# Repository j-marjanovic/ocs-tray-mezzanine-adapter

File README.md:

# OCS Tray Mezzanine Adapter, version 1

## The adapter in action

Here we can see the adapter board connecting the PCIe (x1, over USB) to the FPGA
board, 12V power from the ATX power supply, and I2C to the Raspberry Pi.

## revA

[Schematics as PDF](production/revA/ocp-tray-mezzanine-adapter-v1-revA.pdf)

Known limitations/errors:

  * Samtec connector is rotated by 180 deg - the keying pins on the sides need
    to be trimmed
  * Pin 4 on the USB should be not be connected to the board; it should either
    be trimmed before soldering or the via should be removed
  * The mounting hole is slightly misaligned

## TODO for revB

  * solder mask keep-out for PCIe lanes 7, 8 and 15
  * solder mask keep-out for layer indicators
  * move label R2 (silkscreen over pad)
  * (optional) labels for SDA, SCL and GND on MEZZ I2C connector
  * mode capacitors C1 and C5 to the other side (shorter traces)
  * pin 1 and 4 on the USB connector carry the PCIe signals, fix the connections
  * the LED for the mezzanine present signals has wrong polarity, it should be
    powered from 3V3
  * fix the orientation of the Samtec connector
  * fix the alignment of the mounting hole

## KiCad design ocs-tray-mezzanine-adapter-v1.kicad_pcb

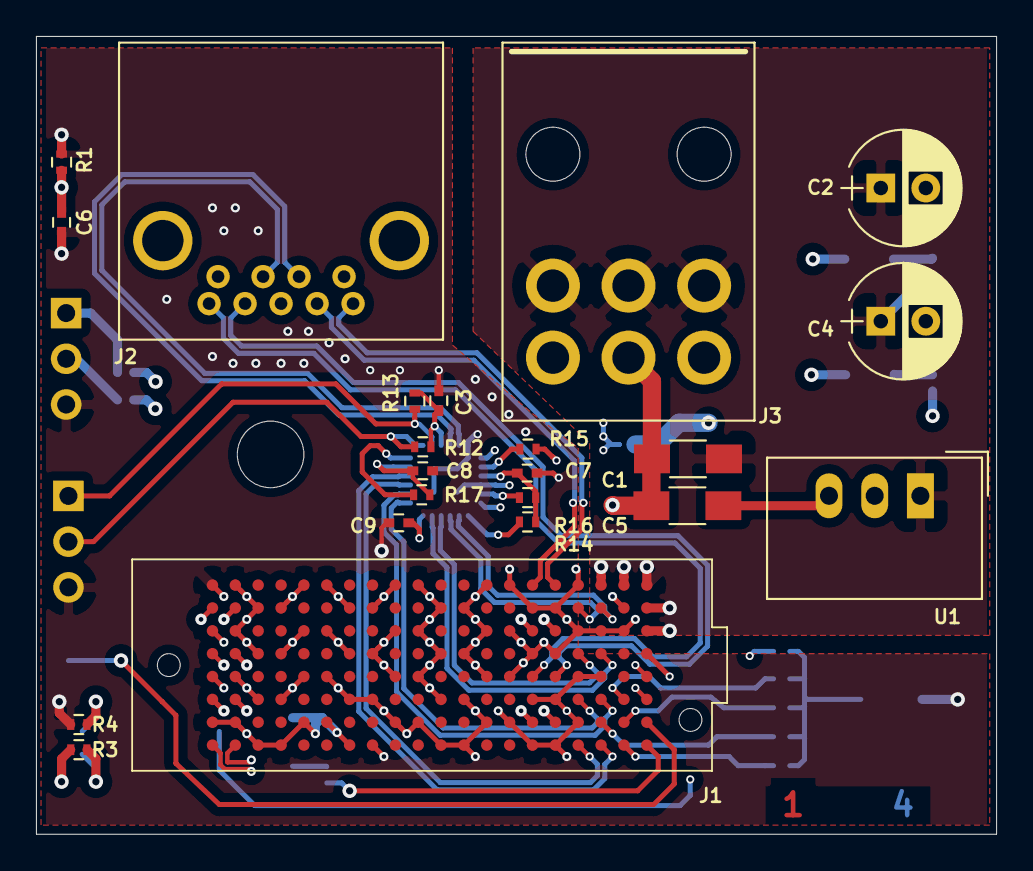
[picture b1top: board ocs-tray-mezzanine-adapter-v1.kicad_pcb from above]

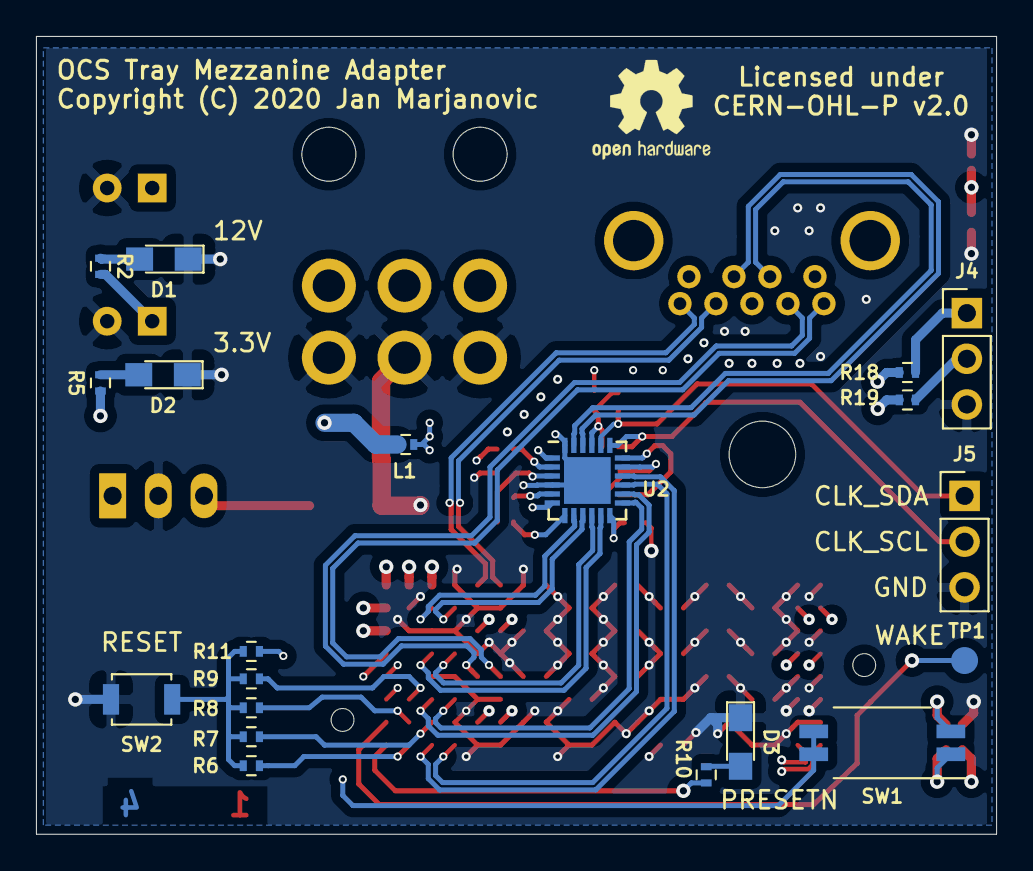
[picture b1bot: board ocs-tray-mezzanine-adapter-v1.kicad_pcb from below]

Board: 4 copper layers, 53.3 x 44.3 mm, 43 parts (20 on the bottom side), 40 nets.

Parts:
C1, C5: 10u; C_1206_HandSoldering
C2, C4: 100uA; CP_Radial_D6.3mm_P2.50mm
C3, C6, C7, C8, C9: 100n; C_0402
D1, D2, D3: LED; LED_0805_HandSoldering
H1: MountingHole; MountingHole_3.7mm
J1: SEAF-20-06.5-L-08-2-A-K-TR; samtec_searay
J2: USB3_A; 692121030100
J3: 45558-0003
J4, J5: Conn_01x03; Pin_Header_Straight_1x03_Pitch2.54mm
L1: L_Core_Ferrite_Small; L_0402
R1: 1M; R_0402
R2, R10, R11, R12, R13, R14, R15, R16, R17, R18, R19: 10k; R_0402
R3, R4, R5, R6, R7, R8, R9: 1k; R_0402
SW1: SW_DIP_x02; SW_DIP_x2_W7.62mm_Slide_Copal_CHS-B
SW2: SW_Push; SW_SPST_B3U-1000P
TP1: TestPoint; Measurement_Point_Round-SMD-Pad_Small
U1: TSR_1-2433; Converter_DCDC_TRACO_TSR-1_THT
U2: SI53154; QFN-24-1EP_4x4mm_Pitch0.5mm

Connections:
+3V3: C5.1, L1.1, R3.2, R5.1, R11.2, R18.1, R19.1, U1.3
+12V: C1.1, C2.1, C4.1, J1.A18, J1.A19, J1.A20, J1.B20, J1.C20, J3.1, J3.2, J3.3, R2.2, U1.1
/MEZZ_EN: J1.E20, SW1.3, SW1.4
/MEZZ_SCL: J1.D20, J4.2, R19.2
/MEZZ_SDA: J1.F20, J4.1, R18.2
/PCIE_CLK_0_N: J1.B18, U2.8
/PCIE_CLK_0_P: J1.B17, U2.9
/PCIE_CLK_1_N: J1.D18, U2.11
/PCIE_CLK_1_P: J1.D17, U2.10
/PCIE_CLK_2_N: J1.F18, U2.14
/PCIE_CLK_2_P: J1.F17, U2.13
/PCIE_CLK_3_N: J1.H18, U2.16
/PCIE_CLK_3_P: J1.H17, U2.15
/PCIE_CLK_N: J2.2, U2.22
/PCIE_CLK_P: J2.3, U2.23
/PCIE_PRSNT_N: J1.H20, R10.2
/PCIE_RSNT_0_N: J1.F19, R9.2
/PCIE_RSNT_1_N: J1.G19, R8.2
/PCIE_RSNT_2_N: J1.G18, R7.2
/PCIE_RSNT_3_N: J1.H19, R6.2
/PCIE_RX_0_N: J1.A16, J2.9
/PCIE_RX_0_P: J1.A15, J2.8
/PCIE_TX_0_N: J1.E16, J2.6
/PCIE_TX_0_P: J1.E15, J2.5
/PCIE_WAKE_N: J1.G20, TP1.1
/USB_GND: C6.1, J2.4, J2.7, J2.10, R1.1
/VCC_SI53154: C3.1, C7.1, C8.1, C9.1, L1.2, R12.2, R13.2, R14.2, R15.2, R16.2, R17.2, U2.1, U2.3, U2.6, U2.12, U2.17, U2.21
GND: C1.2, C2.2, C3.2, C4.2, C5.2, C6.2, C7.2, C8.2, C9.2, D1.1, D2.1, D3.1, J1.A1, J1.A2, J1.A5, J1.A6, J1.A9, J1.A10, J1.A13, J1.A14, J1.A17, J1.B3, J1.B4, J1.B7, J1.B8, J1.B11, J1.B12, J1.B15, J1.B16, J1.B19, J1.C1, J1.C2, J1.C5, J1.C6, J1.C9, J1.C10, J1.C13, J1.C14, J1.C17, J1.C18, J1.C19, J1.D3, J1.D4, J1.D7, J1.D8, J1.D11, J1.D12, J1.D15, J1.D16, J1.E1, J1.E2, J1.E5, J1.E6, J1.E9, J1.E10, J1.E13, J1.E14, J1.E17, J1.E18, J1.F3, J1.F4, J1.F7, J1.F8, J1.F11, J1.F12, J1.F15, J1.F16, J1.G1, J1.G2, J1.G5, J1.G6, J1.G9, J1.G10, J1.G13, J1.G14, J1.G17, J1.H3, J1.H4, J1.H7, J1.H8, J1.H11, J1.H12, J1.H15, J1.H16, J3.4, J3.5, J3.6, J4.3, J5.3, R1.2, R4.2, SW2.2, U1.2, U2.4, U2.24, U2.25
unnamed: D1.2, R2.1
unnamed: D2.2, R5.2
unnamed: D3.2, R10.1
unnamed: J5.1, R13.1, U2.20
unnamed: J5.2, R12.1, U2.19
unnamed: R3.1, SW1.1
unnamed: R4.1, SW1.2
unnamed: R6.1, R7.1, R8.1, R9.1, R11.1, SW2.1
unnamed: R14.1, U2.7
unnamed: R15.1, U2.2
unnamed: R16.1, U2.5
unnamed: R17.1, U2.18

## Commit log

2020-05-09 Final schematics, PCB almost done
2020-05-09 Revision A done
2020-05-09 Add LICENSE
2020-05-10 Add a list of TODOs for next revision
2020-05-10 Add schematics in PDF format
2020-05-10 Fix a link in the README.md
2020-05-31 Add notes from the bringup of revA board
2020-05-31 Reduce image size

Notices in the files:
ocs-tray-mezzanine-adapter-v1.kicad_pcb:
Licensed under
CERN-OHL-P v2.0
Copyright (C) 2020 Jan Marjanovic
